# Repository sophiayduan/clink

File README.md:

# Clink

A e-ink display with WiFi connectivity and a rotary encoder for navigation. It can be powered via USB-C or a LiPo battery.

The e-ink display I will be using includes red and yellow, which will help me create cool clock displays!

## PCB:

## CAD: 
(there are no screws/nuts since that fusion feature broke for me after updating it)

<details>
  <summary>BOM</summary>

| Item            | Description                            | Quantity or MOQ | Cost (USD) shipping included | Comment                                                                                                       | Link                                                                                                                                                                                                                                                                                                                                                                                                                                                                                                                                                                                                                                                                                                                                                                                                                                                                                                                                                                                   |
| --------------- | -------------------------------------- | --------------- | ---------------------------- | ------------------------------------------------------------------------------------------------------------- | -------------------------------------------------------------------------------------------------------------------------------------------------------------------------------------------------------------------------------------------------------------------------------------------------------------------------------------------------------------------------------------------------------------------------------------------------------------------------------------------------------------------------------------------------------------------------------------------------------------------------------------------------------------------------------------------------------------------------------------------------------------------------------------------------------------------------------------------------------------------------------------------------------------------------------------------------------------------------------------- |
| LiPo Battery    | 3.7V                                   | 1               | 5.4                          |                                                                                                               | [https://www.aliexpress.com/item/1005008218024646.html?spm=a2g0o.productlist.main.5.7936qlAtqlAt1N&algo_pvid=981c4458-8bf4-4fb1-8ea7-a434008608e6&algo_exp_id=981c4458-8bf4-4fb1-8ea7-a434008608e6-4&pdp_ext_f=%7B%22order%22%3A%221711%22%2C%22eval%22%3A%221%22%7D&pdp_npi=4%40dis%21USD%2111.55%210.99%21%21%2182.69%217.07%21%402101e9a217540058453494668eba15%2112000044269020516%21sea%21CA%212723362424%21ACX&curPageLogUid=6RrSpH2iOTBO&utparam-url=scene%3Asearch%7Cquery_from%3A](https://www.aliexpress.com/item/1005008218024646.html?spm=a2g0o.productlist.main.5.7936qlAtqlAt1N&algo_pvid=981c4458-8bf4-4fb1-8ea7-a434008608e6&algo_exp_id=981c4458-8bf4-4fb1-8ea7-a434008608e6-4&pdp_ext_f=%7B%22order%22%3A%221711%22%2C%22eval%22%3A%221%22%7D&pdp_npi=4%40dis%21USD%2111.55%210.99%21%21%2182.69%217.07%21%402101e9a217540058453494668eba15%2112000044269020516%21sea%21CA%212723362424%21ACX&curPageLogUid=6RrSpH2iOTBO&utparam-url=scene%3Asearch%7Cquery_from%3A) |
| PCB (PCBA)      |                                        | 5 boards 2 pcba | 49.64                        | I dont know to reflow solder, hence why I chose PCBA. Let me know if that is an issue and I guess I'll learn. |                                                                                                                                                                                                                                                                                                                                                                                                                                                                                                                                                                                                                                                                                                                                                                                                                                                                                                                                                                                        |
| E-paper display | Comes with connection and driver board | 1               | 23                           | $5 was shipping                                                                                               | [https://www.waveshare.com/3.5inch-e-paper-module-g.htm](https://www.waveshare.com/3.5inch-e-paper-module-g.htm)                                                                                                                                                                                                                                                                                                                                                                                                                                                                                                                                                                                                                                                                                                                                                                                                                                                                       |

Total Cost: 78.04 USD (MADE MISTAKE ON THE FORM IT IS $78 NOT $68)
</details>

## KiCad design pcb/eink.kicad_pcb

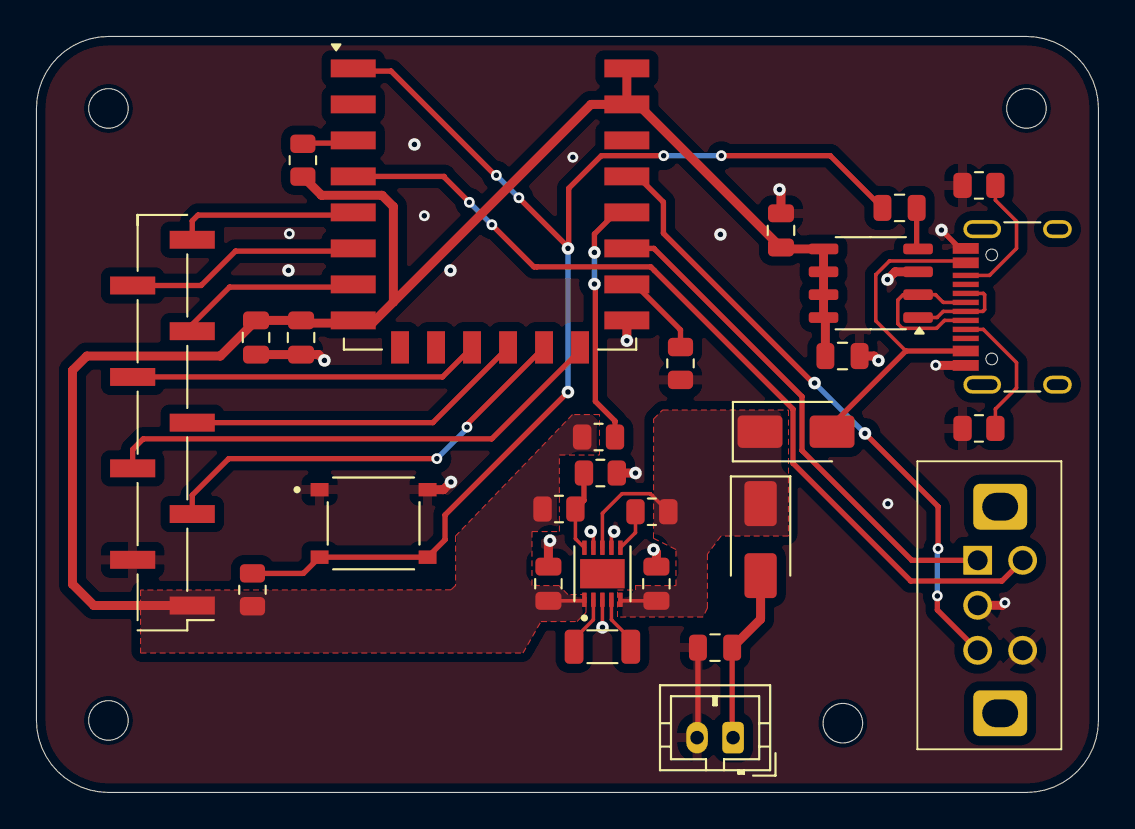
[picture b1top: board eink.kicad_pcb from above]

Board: 2 copper layers, 59.0 x 42.0 mm, 32 parts (0 on the bottom side), 28 nets.

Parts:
BT1: Battery_Cell; JST_PH_B2B-PH-K_1x02_P2.00mm_Vertical
C1, C7, C8: 10uF; C_0805_2012Metric
C2, C4, C5, C6: 100nF; C_0805_2012Metric
C9: 20uF; C_0805_2012Metric
D6, D7: D_Schottky; D_SMA
H1, H2, H3, H4: MountingHole; MountingHole_2.2mm_M2
J1: USB_C_Receptacle_USB2.0_16P; USB_C_Receptacle_HRO_TYPE-C-31-M-12
J3: E-paper Display; PinHeader_1x09_P2.54mm_Vertical_SMD_Pin1Left
L1: 2.2uH; L_1206_3216Metric
R1, R2, R3, R4, R7: 10k; R_0805_2012Metric
R5: 487k; R_0805_2012Metric
R6: 86.6k; R_0805_2012Metric
R8, R9: 5k1; R_0805_2012Metric
SW1: SW_Push; SW_TS-1187A-B-A-B
SW2: RotaryEncoder_Switch_MP; EC11J
U1: ESP-12F; ESP-12E
U3: RT6150AGQW; SON50P300X300X80-11N
U4: CH340N; SOP-8_3.9x4.9mm_P1.27mm

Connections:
+BATT: BT1.1 (+), C7.1, D7.2 (A)
/BUSY: J3.8, U1.6 (GPIO12)
/CLK: J3.4, U1.14 (SCLK)
/CS: J3.5, U1.12 (GPIO10)
/DC: J3.6, U1.11 (GPIO9)
/DIN: J3.3, U1.13 (MOSI)
/PWR: J3.9, U1.5 (GPIO14)
/RESET: C4.1, R3.2, SW1.2, U1.1 (~RST)
/RST: J3.7, U1.7 (GPIO13)
/UD+: J1.A6 (D+), J1.B6 (D+), U4.1 (UD+)
/UD-: J1.A7 (D-), J1.B7 (D-), U4.2 (UD-)
GND: BT1.2 (-), C1.2, C2.2, C5.2, C6.2, C7.2, C8.2, C9.2, J1.A1 (GND), J1.A12 (GND), J1.B1 (GND), J1.B12 (GND), J3.2, R1.2, R6.2, R8.2, R9.1, SW1.1, SW2.C, SW2.S2, U1.15 (GND), U3.3 (GND), U3.7 (PS), U3.9 (GND), U4.3 (GND)
unnamed: D6.2 (A), J1.A4 (VBUS), J1.A9 (VBUS), J1.B4 (VBUS), J1.B9 (VBUS)
unnamed: J1.A5 (CC1), R8.1
unnamed: J1.B5 (CC2), R9.2
unnamed: R4.2, U1.3 (EN)
unnamed: R2.1, U1.18 (GPIO0)
unnamed: SW2.A, U1.17 (GPIO2)
unnamed: SW2.B, U1.19 (GPIO4)
unnamed: R1.1, U1.16 (GPIO15)
unnamed: SW2.S1, U1.4 (GPIO16)
unnamed: R7.1, U3.6 (EN)
unnamed: R5.2, R6.1, U3.10 (FB)
unnamed: L1.1, U3.4 (LX1)
unnamed: L1.2, U3.2 (LX2)
unnamed: C4.2, U4.4 (~RTS)
VBUS: C8.1, D6.1 (K), D7.1 (K), R7.2, U3.5 (VIN), U3.8 (VINA)
VCC: C1.1, C2.1, C5.1, C6.1, C9.1, J3.1, R2.2, R3.1, R4.1, R5.1, U1.8 (VCC), U1.21 (GPIO3/RXD), U1.22 (GPIO1/TXD), U3.1 (VOUT), U4.5 (VCC), U4.6 (TXD), U4.7 (RXD), U4.8 (V3)

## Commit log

2025-08-01 firmware
2025-08-04 new step files
